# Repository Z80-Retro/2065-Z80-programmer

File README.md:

An in-circuit programmer for the FLASH on a [2063-Z80](https://github.com/johnwinans/2063-Z80) board.

* A youtube playlist discussing this project and how to build your own can be found in [John's Basement](https://www.youtube.com/watch?v=oekucjDcNbA&list=PL3by7evD3F51Cf9QnsAEdgSQ4cz7HQZX5)
* A PDF version of the schematic can be found [here](2065-Z80-programmer.pdf).
* Here is the as-built [BOM](2065-Z80-programmer.md) with links to the datasheets for all the parts.
* Here is another [BOM](2065-Z80-programmer-sockets.md) with links to sockets for the chips.
* A Raspberry PI application for this board can be found in the [pi](pi) directory.
* To configure a new PI for use with this programmer board as well as to develop Z80 code 
for the Z80 Retro board, see this [PI Setup Guide](https://github.com/johnwinans/raspberry-pi-install)

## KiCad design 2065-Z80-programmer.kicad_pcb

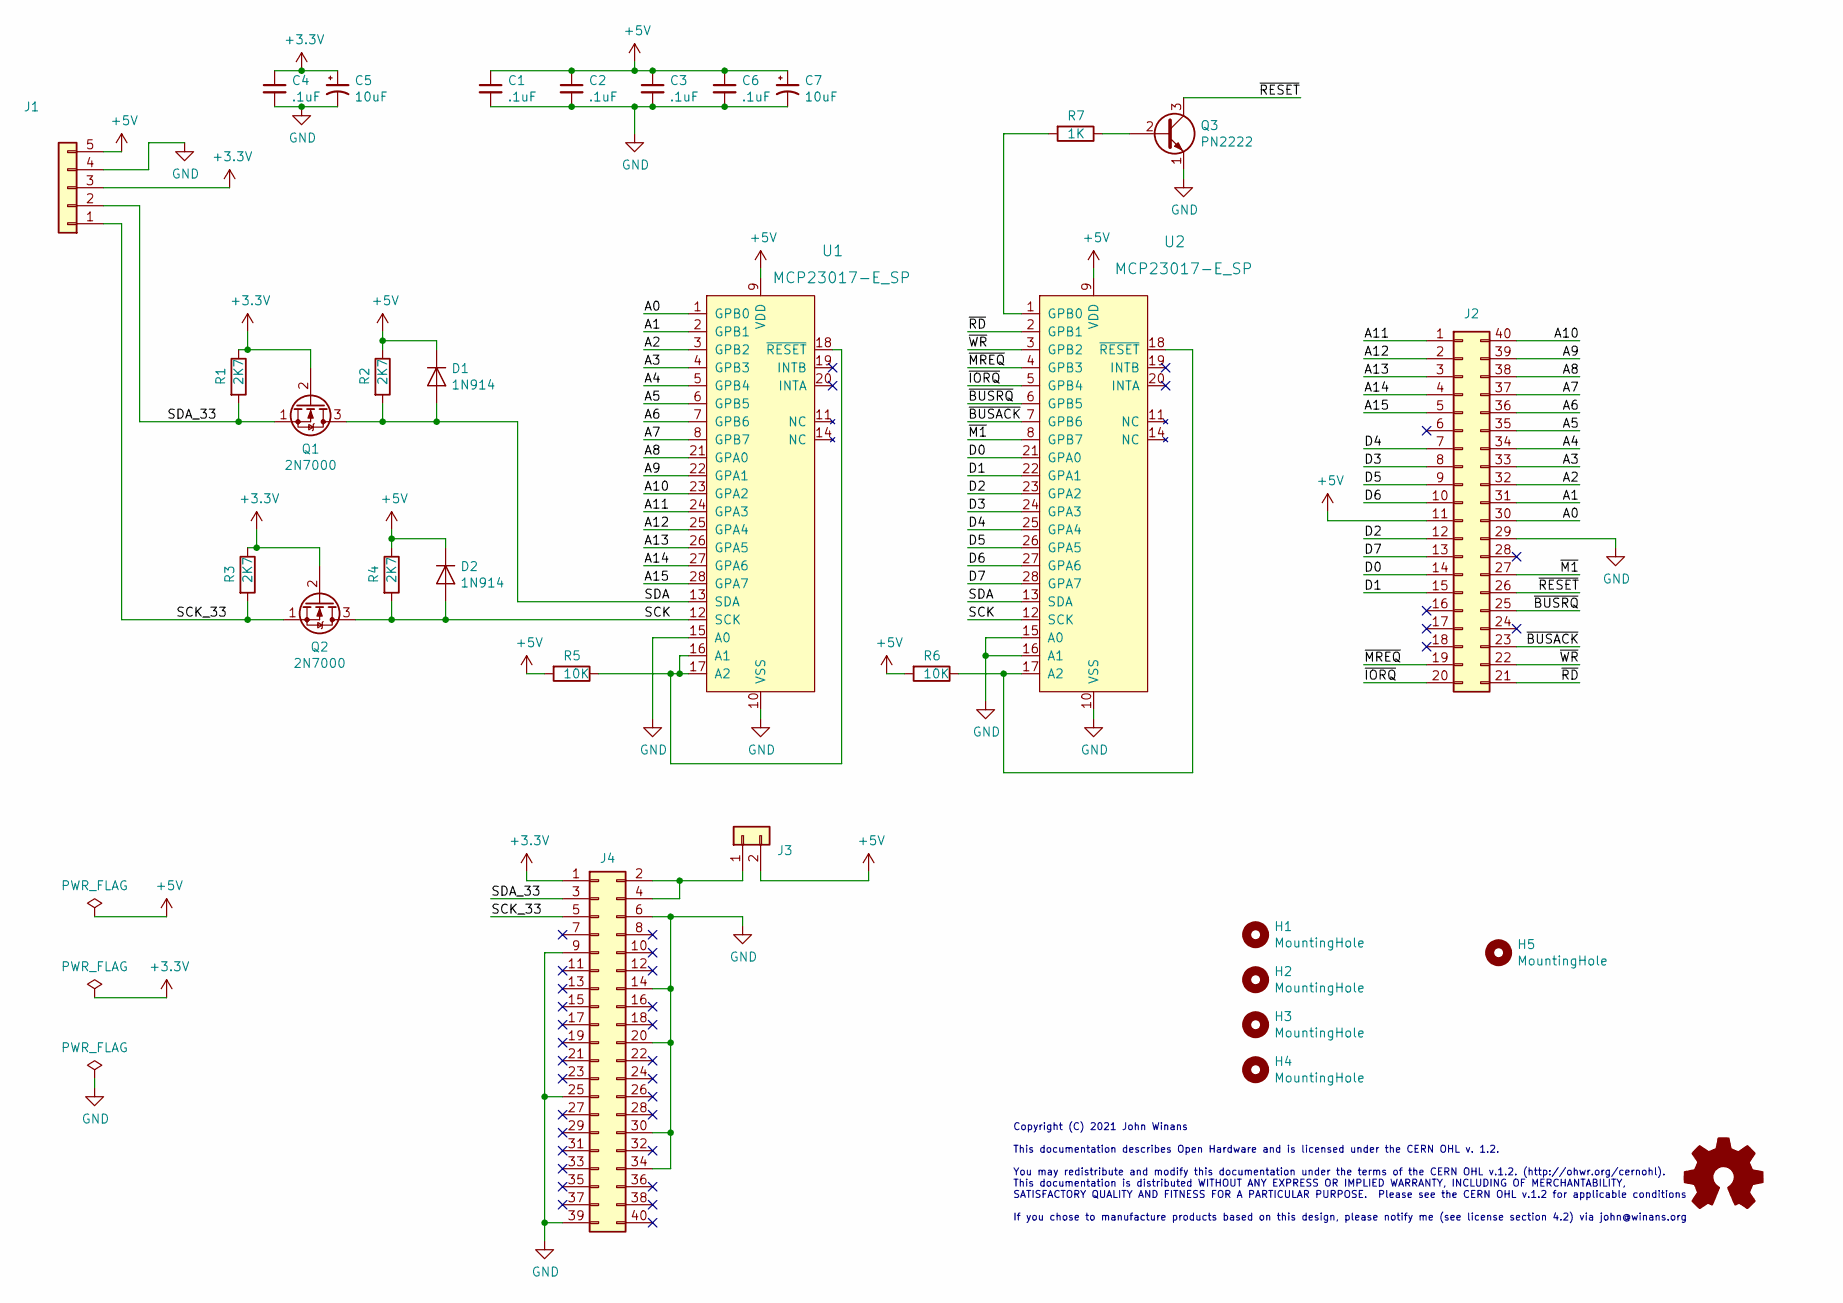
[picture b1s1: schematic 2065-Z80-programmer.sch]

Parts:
C1, C2, C3, C4, C6: .1uF; C_Disc_D3.8mm_W2.6mm_P2.50mm; Digi-Key_PN 399-9859-1-ND‎
C5, C7: 10uF; CP_Radial_D5.0mm_P2.50mm; MPN ECE-A1EKS100; Digi-Key_PN P975-ND
D1, D2: 1N914; D_DO-35_SOD27_P7.62mm_Horizontal; MPN 1N4148TR; Digi-Key_PN 1N4148FSCT-ND
H1, H2, H3, H4, H5: MountingHole; MountingHole_2.7mm_M2.5_DIN965
J1: Conn_01x05; PinHeader_1x05_P2.54mm_Vertical; Digi-Key_PN S1211EC-05-ND
J2: Conn_02x20_Counter_Clockwise; PinSocket_2x20_P2.54mm_Vertical_clockwise; MPN PPTC202LFBN-RC; Digi-Key_PN S6104-ND
J3: Conn_01x02; PinHeader_1x02_P2.54mm_Vertical; Digi-Key_PN S1011EC-02-ND
J4: Conn_02x20_Odd_Even; PinHeader_2x20_P2.54mm_Vertical; Digi-Key_PN S2011EC-20-ND
LOGO10: Logo_Open_Hardware_Small; OSHW-Logo_11.4x12mm_SilkScreen
Q1, Q2: 2N7000; TO-92; MPN 2N7000TA; Digi-Key_PN 2N7000TACT-ND
Q3: PN2222; TO-92L; Digi-Key_PN 1514-PN2222APBFREE-ND
R1, R2, R3, R4: 2K7; R_Axial_DIN0204_L3.6mm_D1.6mm_P5.08mm_Horizontal; MPN CF18JT2K70; Digi-Key_PN CF18JT2K70CT-ND
R5, R6: 10K; R_Axial_DIN0204_L3.6mm_D1.6mm_P5.08mm_Horizontal; MPN CF18JT10K0; Digi-Key_PN CF18JT10K0CT-ND
R7: 1K; R_Axial_DIN0204_L3.6mm_D1.6mm_P5.08mm_Horizontal; MPN CF18JT1K00; Digi-Key_PN CF18JT1K00CT-ND
U1, U2: MCP23017-E_SP; DIP-28_W7.62mm_Socket; MPN MCP23017-E/SP; Digi-Key_PN MCP23017-E/SP-ND

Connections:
+3V3: C4.1, C5.1, J1.3, J4.1, Q1.2 (G), Q2.2 (G), R1.1, R3.1
+5V: C1.1, C2.1, C3.1, C6.1, C7.1, D1.1 (K), D2.1 (K), J1.5, J2.11, J3.2, R2.1, R4.1, R5.2, R6.2, U1.9 (VDD), U2.9 (VDD)
/A0: J2.30, U1.1 (GPB0)
/A1: J2.31, U1.2 (GPB1)
/A2: J2.32, U1.3 (GPB2)
/A3: J2.33, U1.4 (GPB3)
/A4: J2.34, U1.5 (GPB4)
/A5: J2.35, U1.6 (GPB5)
/A6: J2.36, U1.7 (GPB6)
/A7: J2.37, U1.8 (GPB7)
/A8: J2.38, U1.21 (GPA0)
/A9: J2.39, U1.22 (GPA1)
/A10: J2.40, U1.23 (GPA2)
/A11: J2.1, U1.24 (GPA3)
/A12: J2.2, U1.25 (GPA4)
/A13: J2.3, U1.26 (GPA5)
/A14: J2.4, U1.27 (GPA6)
/A15: J2.5, U1.28 (GPA7)
/D0: J2.14, U2.21 (GPA0)
/D1: J2.15, U2.22 (GPA1)
/D2: J2.12, U2.23 (GPA2)
/D3: J2.8, U2.24 (GPA3)
/D4: J2.7, U2.25 (GPA4)
/D5: J2.9, U2.26 (GPA5)
/D6: J2.10, U2.27 (GPA6)
/D7: J2.13, U2.28 (GPA7)
/SCK: D2.2 (A), Q2.3 (D), R4.2, U1.12 (SCK), U2.12 (SCK)
/SCK_33: J1.1, J4.5, Q2.1 (S), R3.2
/SDA: D1.2 (A), Q1.3 (D), R2.2, U1.13 (SDA), U2.13 (SDA)
/SDA_33: J1.2, J4.3, Q1.1 (S), R1.2
/~BUSACK: J2.23, U2.7 (GPB6)
/~BUSRQ: J2.25, U2.6 (GPB5)
/~IORQ: J2.20, U2.5 (GPB4)
/~M1: J2.27, U2.8 (GPB7)
/~MREQ: J2.19, U2.4 (GPB3)
/~RD: J2.21, U2.2 (GPB1)
/~RESET: J2.26, Q3.3 (C)
/~WR: J2.22, U2.3 (GPB2)
GND: C1.2, C2.2, C3.2, C4.2, C5.2, C6.2, C7.2, J1.4, J2.29, J4.6, J4.9, J4.14, J4.20, J4.25, J4.30, J4.34, J4.39, Q3.1 (E), U1.10 (VSS), U1.15 (A0), U2.10 (VSS), U2.15 (A0), U2.16 (A1)
unnamed: J3.1, J4.2, J4.4
unnamed: Q3.2 (B), R7.1
unnamed: R5.1, U1.16 (A1), U1.17 (A2), U1.18 (~RESET)
unnamed: R6.1, U2.17 (A2), U2.18 (~RESET)
unnamed: R7.2, U2.1 (GPB0)

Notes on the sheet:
Copyright (C) 2021 John Winans This documentation describes Open Hardware and is licensed under the CERN OHL v. 1.2. You may redistribute and modify this documentation under the terms of the CERN OHL v.1.2. (http://ohwr.org/cernohl). This documentation is distributed WITHOUT ANY EXPRESS OR IMPLIED 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

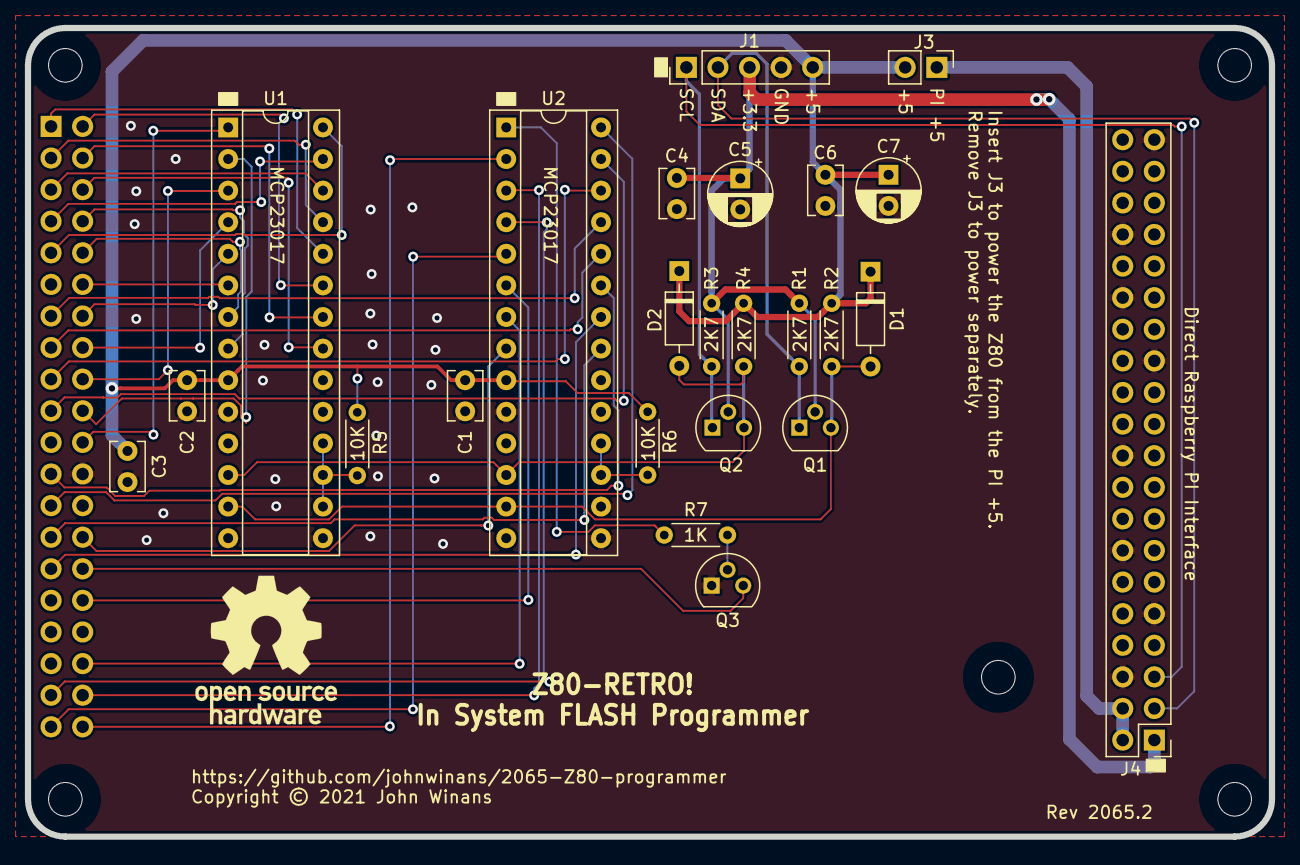
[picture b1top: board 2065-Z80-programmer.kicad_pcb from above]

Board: 2 copper layers, 100.0 x 65.0 mm, 31 parts (1 on the bottom side), 44 nets.

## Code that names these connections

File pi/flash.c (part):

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#define	IO_RESET	(0x01)	///< ALWAYS output
#define	IO_RD		(0x02)	///< output when take over the bus, else input/float
#define	IO_WR		(0x04)	///< output when take over the bus, else input/float
#define	IO_MREQ		(0x08)	///< output when take over the bus, else input/float
#define	IO_IORQ		(0x10)	///< output when take over the bus, else input/float
#define	IO_BUSRQ	(0x20)	///< ALWAYS output
#define	IO_BUSACK	(0x40)	///< ALWAYS input
#define	IO_M1		(0x80)	///< ALWAYS input

// These are used to configure the control ports when transitioning from 
// passive to active control mode (ie, when the Z80 bus is taken over by the
// programmer.  Direction control = 1 for inputs, 0 for outputs.
#define IO_DIR_BUS_CTL_ON	(IO_BUSACK|IO_M1)		// all out (0) except /BUSACK & /M1
#define IO_DIR_BUS_CTL_OFF	(~(IO_RESET|IO_BUSRQ))	// /BUSRQ & RESET = out, all others=in


// These are used to set the direction of all 8 bits of a port to in or out
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	ctl_cache = IO_RESET|IO_BUSRQ; 		// de-assert /BUSRQ and assert RESET
	mcp23017_write_b(iic, I2C_EX2, ctl_cache);	

	// de-assert the RESET (while keeping /BUSRQ signal de-asserted)
	ctl_cache &= ~IO_RESET;				// RESET=0, leave IO_BUSRQ=1
	mcp23017_write_b(iic, I2C_EX2, ctl_cache);
}

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
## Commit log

2021-09-13 Initial import
2021-09-13 Added a picture.
2021-09-21 Ignore zip files.
2021-10-19 Pull up /RESET
2021-10-19 Add 5V clamping diodes to I2C lines Move mounting hole clear of user-1 header
2021-10-19 Update PCB image.
2021-10-19 Add links to YouTube series, BOM, & schematic
2021-10-19 Update sch, pcb, & BOM to match as-built v1.0.
2021-10-19 Correct J2 to female connector.
2021-10-19 minor narrative change
2021-10-19 Shorting block cols were backwards
2021-10-21 Added a working draft of a PI FLASH programming app
2021-10-21 Quick doc on how to run it.
2021-10-21 Cosmetic silkscreen cleanup
2021-10-22 Change Z80 header to socket so looks right in 3D
2021-10-22 Render new 3D image with right connectors
2021-10-22 Remove disembodied NC markers.
2021-10-22 Ignore targets
2021-10-27 doc, speed improvements, proper RESET handling
2021-10-29 Turn on the address bus after /BUSRQ ;-)
2021-10-29 Waveform diagrams of how flash.c controls the bus
2021-10-29 Add note about using i2cdetect
2021-10-29 Add blinky example
2021-10-30 Add some notes on how to configure the PI.
2021-10-30 Remove the local copy of the SD card setup instructions.
2021-10-30 Link to the PI setup repo.
2021-10-30 Don't need sudo with i2cdetect
2021-10-30 Add notes about installing LaTeX to build the doc
2021-10-30 Add a note on how to use evince
2021-11-05 Adjust waveforms to match the as-built code.
2021-11-05 Cleanup doc & RESET control
2021-11-10 Add optimization to skip programming 0xff
2022-06-22 Add 1K value to silkscreen for R7
2022-06-22 Move H5 1mm to the left & ignore scratch files.
2022-06-24 Remove stale driver gerber map files.
2022-08-22 Cast some printf() args for signedness and size
2022-10-19 Add commented-out support for AM29F040B
2022-11-04 typo
2023-02-18 Add meta dir so can use as a template project
2023-03-22 Add remote reset app via Programmer Remove unused #includes
2023-03-29 Change Digikey part numbers on 1x5 header
2025-08-30 use 32-bit addr so not rollover
2025-08-30 off by 1
2026-03-02 Added support for SST39SF040 chip

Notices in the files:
2065-Z80-programmer.kicad_pcb:
Copyright © 2021 John Winans
2065-Z80-programmer.sch:
If you chose to manufacture products based on this design, please notify me (see license section 4.2) via john@winans.org
